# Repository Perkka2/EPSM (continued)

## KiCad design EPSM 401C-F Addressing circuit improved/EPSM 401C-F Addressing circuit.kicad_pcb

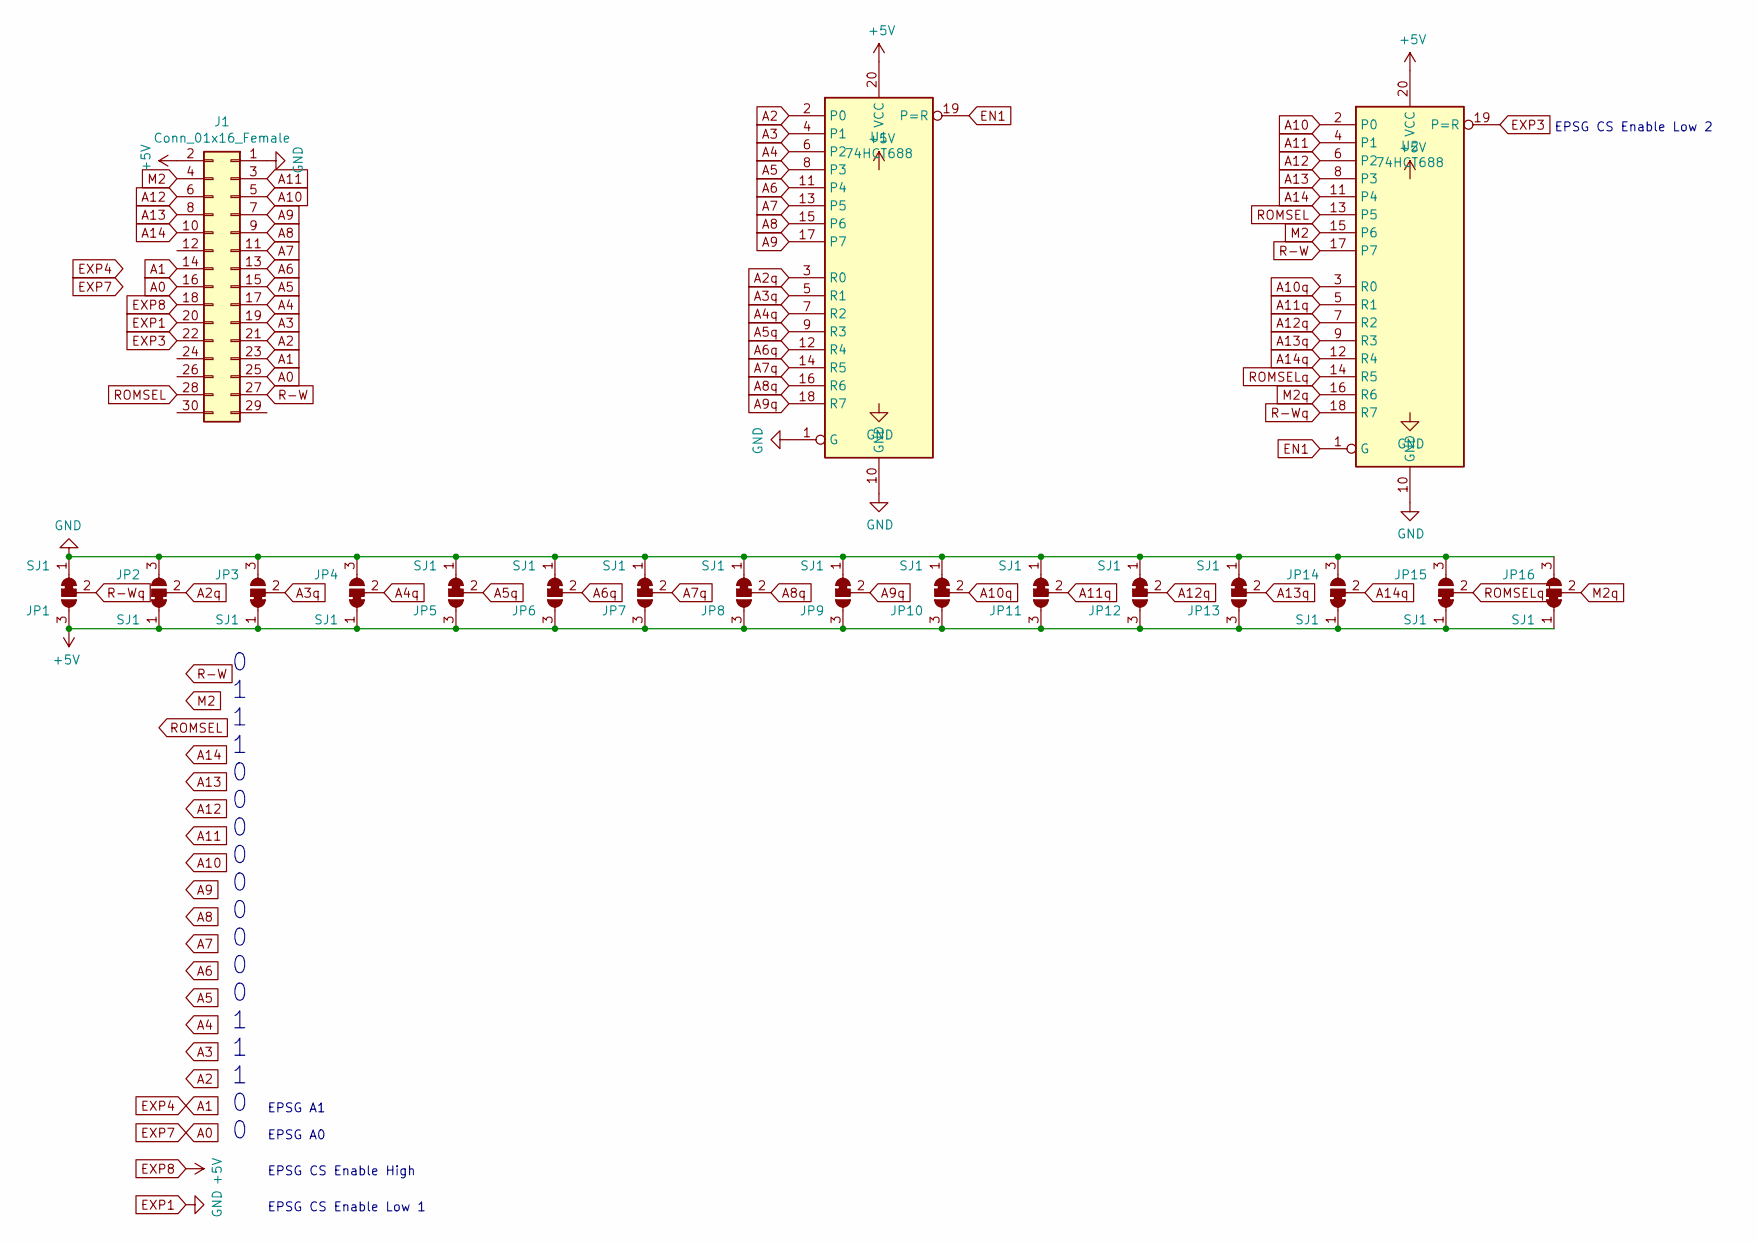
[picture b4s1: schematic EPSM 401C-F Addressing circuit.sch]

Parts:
J1: Conn_01x16_Female; PinSocket_2x15_P2.54mm_Vertical_SMD
JP1, JP2, JP3, JP4, JP5, JP6, JP7, JP8, JP9, JP10, JP11, JP12, JP13, JP14, JP15, JP16: SJ1; SolderJumper-3_P1.3mm_Bridged12_RoundedPad1.0x1.5mm
U1, U2: 74HCT688; SMDIP-20_W9.53mm_Clearance8mm

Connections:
A0: J1.16, J1.25
A1: J1.14, J1.23
A2: J1.21, U1.2 (P0)
A2q: JP2.2 (C), U1.3 (R0)
A3: J1.19, U1.4 (P1)
A3q: JP3.2 (C), U1.5 (R1)
A4: J1.17, U1.6 (P2)
A4q: JP4.2 (C), U1.7 (R2)
A5: J1.15, U1.8 (P3)
A5q: JP5.2 (C), U1.9 (R3)
A6: J1.13, U1.11 (P4)
A6q: JP6.2 (C), U1.12 (R4)
A7: J1.11, U1.13 (P5)
A7q: JP7.2 (C), U1.14 (R5)
A8: J1.9, U1.15 (P6)
A8q: JP8.2 (C), U1.16 (R6)
A9: J1.7, U1.17 (P7)
A9q: JP9.2 (C), U1.18 (R7)
A10: J1.5, U2.2 (P0)
A10q: JP10.2 (C), U2.3 (R0)
A11: J1.3, U2.4 (P1)
A11q: JP11.2 (C), U2.5 (R1)
A12: J1.6, U2.6 (P2)
A12q: JP12.2 (C), U2.7 (R2)
A13: J1.8, U2.8 (P3)
A13q: JP13.2 (C), U2.9 (R3)
A14: J1.10, U2.11 (P4)
A14q: JP14.2 (C), U2.12 (R4)
EN1: U1.19 (P=R), U2.1 (G)
EXP1: J1.1, J1.20, JP1.1 (A), JP2.3 (B), JP3.3 (B), JP4.3 (B), JP5.1 (A), JP6.1 (A), JP7.1 (A), JP8.1 (A), JP9.1 (A), JP10.1 (A), JP11.1 (A), JP12.1 (A), JP13.1 (A), JP14.3 (B), JP15.3 (B), JP16.3 (B), U1.1 (G), U1.10 (GND), U2.10 (GND)
EXP3: J1.22, U2.19 (P=R)
EXP8: J1.2, J1.18, JP1.3 (B), JP2.1 (A), JP3.1 (A), JP4.1 (A), JP5.3 (B), JP6.3 (B), JP7.3 (B), JP8.3 (B), JP9.3 (B), JP10.3 (B), JP11.3 (B), JP12.3 (B), JP13.3 (B), JP14.1 (A), JP15.1 (A), JP16.1 (A), U1.20 (VCC), U2.20 (VCC)
M2: J1.4, U2.15 (P6)
M2q: JP16.2 (C), U2.16 (R6)
R-W: J1.27, U2.17 (P7)
R-Wq: JP1.2 (C), U2.18 (R7)
ROMSEL: J1.28, U2.13 (P5)
ROMSELq: JP15.2 (C), U2.14 (R5)

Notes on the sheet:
0 1 1 1 0 0 0 0 0 0 0 0 0 1 1 1 0 0
EPSG A1
EPSG A0
EPSG CS Enable High
EPSG CS Enable Low 1
EPSG CS Enable Low 2

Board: 2 copper layers, 19 parts (0 on the bottom side), 38 nets, no tracks yet.

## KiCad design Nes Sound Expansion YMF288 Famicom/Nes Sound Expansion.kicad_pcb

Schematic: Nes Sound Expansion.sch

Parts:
BU9480F1: BU9480F; SOIC-8_5.275x5.275mm_P1.27mm
C1, C6, C8, C9: 10uF; C_0504_1310Metric_Pad0.83x1.28mm_HandSolder
C2: 10u; CP_Elec_4x5.3
C3, C4, C5, C7: 68pF; C_0504_1310Metric_Pad0.83x1.28mm_HandSolder
J1: OUT; PinHeader_1x02_P2.54mm_Vertical
J2: EXP 1-30; PinSocket_2x15_P2.54mm_Vertical_SMD
J3: EXP 1-30; Famicon CardEdge
J4: 31-60; Famicon CardEdge
J8: EXP 25-48; Famicon CardEdge
J9: EXP 1-24; Famicon CardEdge
R1, R2, R7: 47k; R_0805_2012Metric_Pad1.20x1.40mm_HandSolder
R3: 4.7k; R_0805_2012Metric_Pad1.20x1.40mm_HandSolder
R4, R5, R8, R9, R12, R13, R14: 1k; R_0805_2012Metric_Pad1.20x1.40mm_HandSolder
R6: 3k; R_0805_2012Metric_Pad1.20x1.40mm_HandSolder
U1: 74LS139; SOIC-16_3.9x9.9mm_P1.27mm
U2: 74LS132; SOIC-14_3.9x8.7mm_P1.27mm
U3: LM321; SOT-23-5
U6, U7: 74LS174; SOIC-16_3.9x9.9mm_P1.27mm
U8, U9, U10: 74LS257; SOIC-16_3.9x9.9mm_P1.27mm
X1: CXO_DIP8; Oscillator_SMD_SeikoEpson_SG8002CA-4Pin_7.0x5.0mm_HandSolde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
YMF288: YMF288

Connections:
4016_EN: R12.2, R13.2, U7.15 (Q5), U8.1 (S), U9.1 (S), U10.1 (S)
+5V: BU9480F1.8, J2.2, J4.1, J8.1, R1.1, R4.1, U1.16 (VCC), U2.14 (VCC), U3.5 (V+), U6.16 (VCC), U7.14 (D5), U7.16 (VCC), U8.16 (VCC), U9.16 (VCC), U10.16 (VCC), X1.4 (VCC), YMF288.12, YMF288.19, YMF288.22, YMF288.27
+5VA: J3.30, J9.30
A0: J2.25, J3.13, J9.13
A0_Chip: U10.7 (Zb), YMF288.20
A0_buf: U6.12 (Q4), U10.6 (I1b)
A1: J2.23, J3.12, J9.12
A1_Chip: U10.4 (Za), YMF288.21
A1_buf: U6.15 (Q5), U10.3 (I1a)
A2: J2.21, J3.11, J9.11
A3: J2.19, J3.10, J9.10
A4: J2.17, J3.9, J9.9
A5: J2.15, J3.8, J9.8
A6: J2.13, J3.7, J9.7
A7: J2.11, J3.6, J9.6
A8: J2.9, J3.5, J9.5
A9: J2.7, J3.4, J9.4
A10: J2.5, J3.3, J9.3
A11: J2.3, J3.2, J9.2
A12: J2.6, J4.3, J8.3
A13: J2.8, J4.4, J8.4
A14: J2.10, J4.5, J8.5
Addr_A1: J2.14, U10.2 (I0a)
Addr_A13: J2.16, U10.5 (I0b)
Addr_A14: J2.18, U1.14 (A0)
Addr_R-W: J2.22, U1.13 (A1)
Addr_ROMSEL: J2.20, U1.15 (E)
Aud: J4.15, J8.15
AudIn: J8.16, R6.1, R9.1
CIRAM_A10: J3.18, J9.18
CIRAM_CE: J4.18, J8.18
CS_: U1.11 (O1), U10.14 (I0c)
CS_Chip: U10.12 (Zc), YMF288.17
CS_buf: U2.6, U10.13 (I1c)
D0: J4.13, J8.13, U9.2 (I0a)
D0_Chip: U9.4 (Za), YMF288.2
D0_buf: U7.2 (Q0), U9.3 (I1a)
D1: J4.12, J8.12, U9.5 (I0b)
D1_Chip: U9.7 (Zb), YMF288.3
D1_buf: U7.5 (Q1), U9.6 (I1b)
D2: J4.11, J8.11, U6.14 (D5), U9.14 (I0c)
D2_Chip: U9.12 (Zc), YMF288.4
D2_buf: U7.7 (Q2), U9.13 (I1c)
D3: J4.10, J8.10, U6.13 (D4), U9.11 (I0d)
D3_Chip: U9.9 (Zd), YMF288.5
D3_buf: U7.10 (Q3), U9.10 (I1d)
D4: J4.9, J8.9, U6.3 (D0), U7.3 (D0), U8.2 (I0a)
D4_Chip: U8.4 (Za), YMF288.6
D4_buf: U6.2 (Q0), U8.3 (I1a)
D5: J4.8, J8.8, U6.4 (D1), U7.4 (D1), U8.5 (I0b)
D5_Chip: U8.7 (Zb), YMF288.7
D5_buf: U6.5 (Q1), U8.6 (I1b)
D6: J4.7, J8.7, U6.6 (D2), U7.6 (D2), U8.14 (I0c)
D6_Chip: U8.12 (Zc), YMF288.8
D6_buf: U6.7 (Q2), U8.13 (I1c)
D7: J4.6, J8.6, U6.11 (D3), U7.11 (D3), U8.11 (I0d)
D7_Chip: U8.9 (Zd), YMF288.9
D7_buf: U6.10 (Q3), U8.10 (I1d)
FF_Reset: U2.8, U6.1 (~Mr), U7.1 (~Mr)
GND: BU9480F1.3, C1.1, C2.2, C3.1, C4.1, C5.1, C7.1, C8.2, J1.1, J2.1, J3.1, J9.1, R2.2, U1.1 (E), U1.8 (GND), U2.7 (GND), U3.2 (V-), U6.8 (GND), U7.8 (GND), U8.8 (GND), U8.15 (OE), U9.8 (GND), U9.15 (OE), U10.8 (GND), U10.15 (OE), X1.2 (GND), YMF288.1, YMF288.14, YMF288.16, YMF288.18
GND1: J3.16, J9.16
IRQ: J3.15, J9.15, YMF288.15
M2: J2.4, J4.2, J8.2
unnamed: BU9480F1.1, R8.2
unnamed: BU9480F1.2, C2.1
unnamed: BU9480F1.4, R5.1
unnamed: BU9480F1.5, YMF288.26
unnamed: BU9480F1.6, YMF288.24
unnamed: BU9480F1.7, YMF288.23
unnamed: C1.2, R4.2, YMF288.11
unnamed: C3.2, R12.1, U2.4
unnamed: C4.2, R13.1, U2.1, U2.2
unnamed: C5.2, R14.1, U2.12, U2.13
unnamed: C6.1, R5.2, R8.1
unnamed: C6.2, C7.2, R1.2, R2.1, U3.1 (+)
unnamed: C8.1, R3.2
unnamed: C9.1, R9.2
unnamed: C9.2, R7.2, U3.4
unnamed: J4.16, R6.2
unnamed: R3.1, R7.1, U3.3 (-)
unnamed: R14.2, U2.3, U2.5
unnamed: U2.9, U2.10, U2.11
unnamed: X1.3 (OUT), YMF288.28
OUT1: J1.2, U1.2 (A0), U1.3 (A1), U6.9 (Cp)
OUT1_: U1.7 (O3), U7.9 (Cp)
PPU_A0: J3.25, J9.25
PPU_A1: J3.24, J9.24
PPU_A2: J3.23, J9.23
PPU_A3: J3.22, J9.22
PPU_A4: J3.21, J9.21
PPU_A5: J3.20, J9.20
PPU_A6: J3.19, J9.19
PPU_A7: J4.20, J8.20
PPU_A8: J4.21, J8.21
PPU_A9: J4.22, J8.22
PPU_A10: J4.23, J8.23
PPU_A11: J4.24, J8.24
PPU_A12: J4.25, J8.25
PPU_A13: J4.26, J8.26
PPU_A13_: J4.19, J8.19
PPU_D0: J3.26, J9.26
PPU_D1: J3.27, J9.27
PPU_D2: J3.28, J9.28
PPU_D3: J3.29, J9.29
PPU_D4: J4.30, J8.30
PPU_D5: J4.29, J8.29
PPU_D6: J4.28, J8.28
PPU_D7: J4.27, J8.27
PPU_RD: J3.17, J9.17
PPU_WR: J4.17, J8.17
R-W: J2.27, J3.14, J9.14
ROMSEL: J2.28, J4.14, J8.14

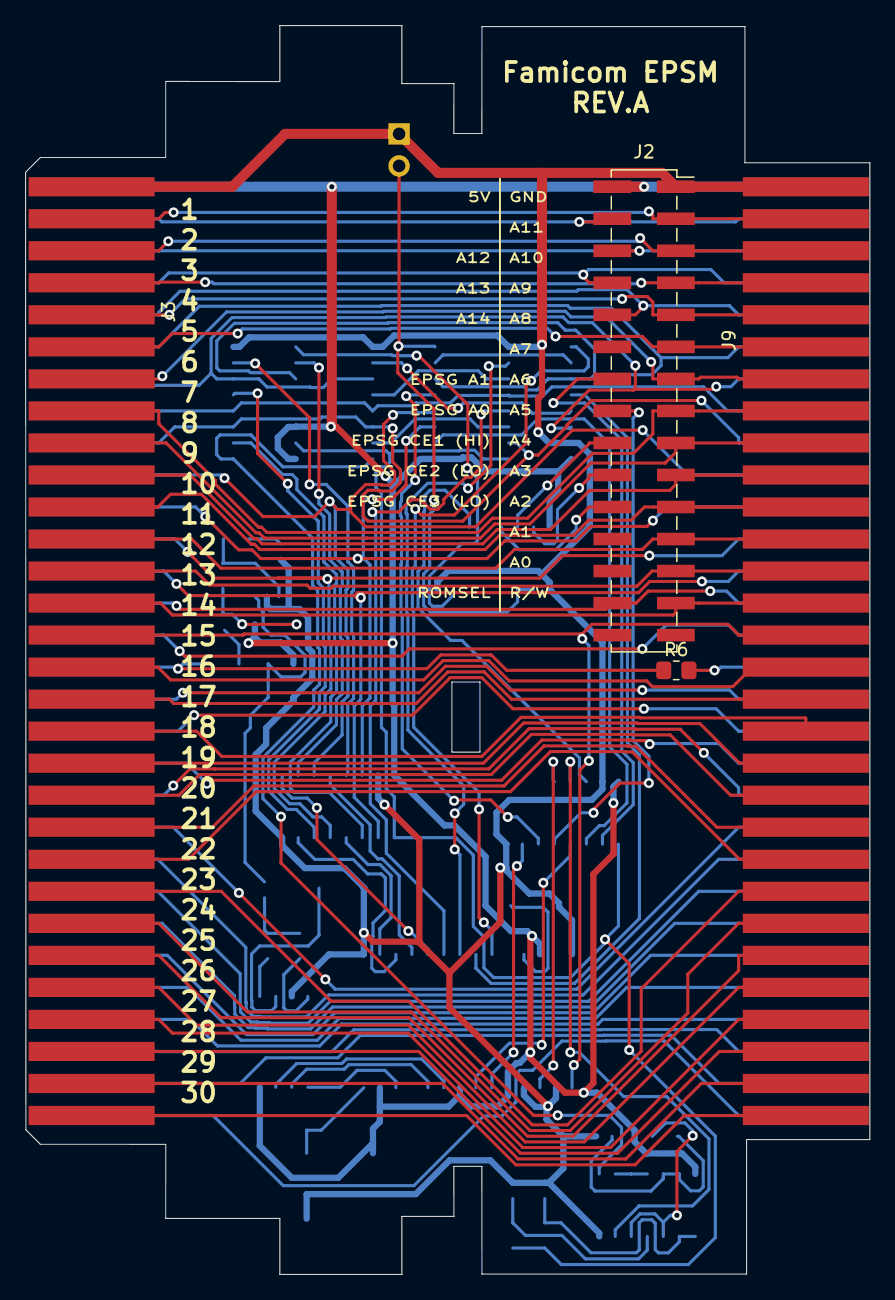
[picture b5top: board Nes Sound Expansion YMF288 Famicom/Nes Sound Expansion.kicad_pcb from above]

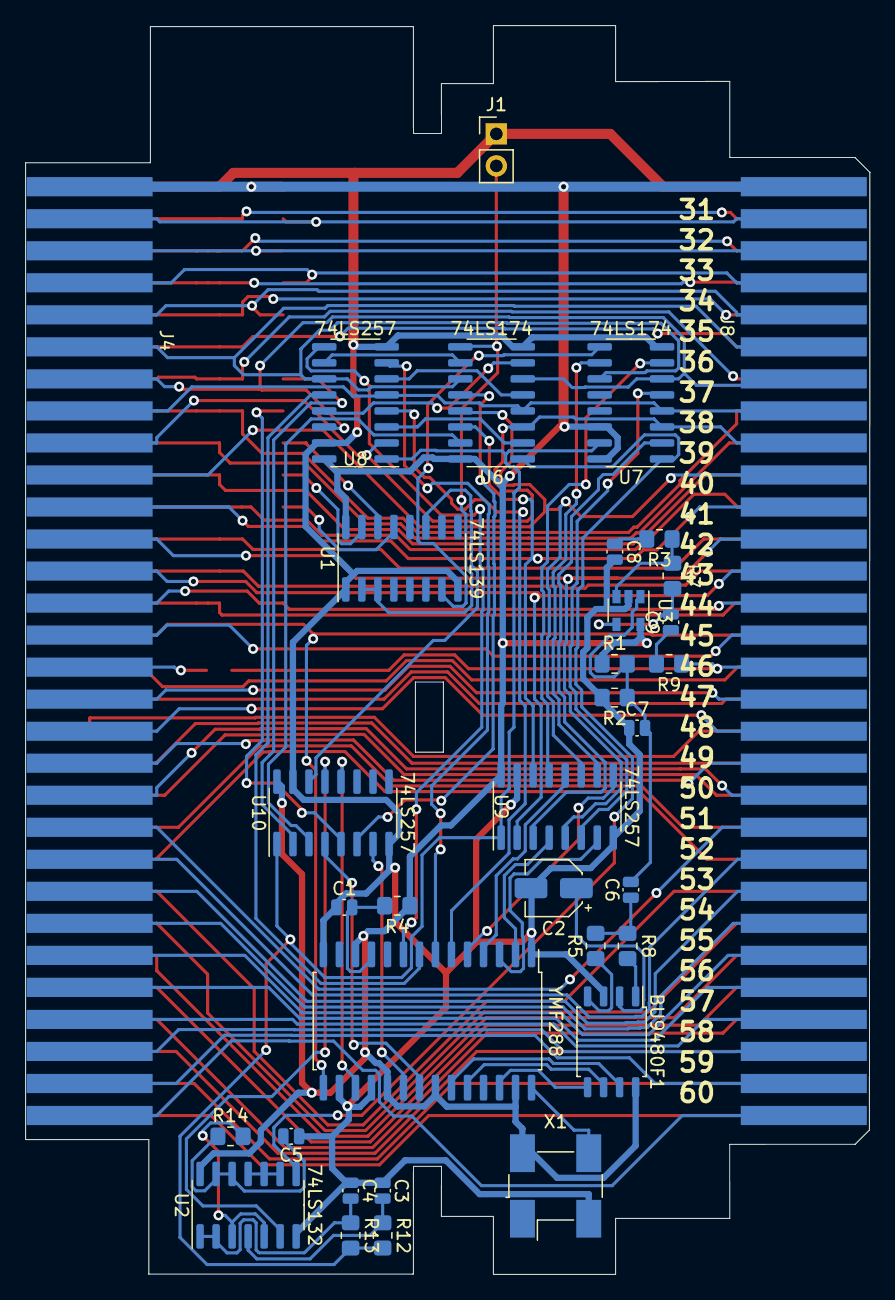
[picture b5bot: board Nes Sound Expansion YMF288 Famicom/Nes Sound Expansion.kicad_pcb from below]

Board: 2 copper layers, 67.0 x 99.0 mm, 38 parts (34 on the bottom side), 112 nets.

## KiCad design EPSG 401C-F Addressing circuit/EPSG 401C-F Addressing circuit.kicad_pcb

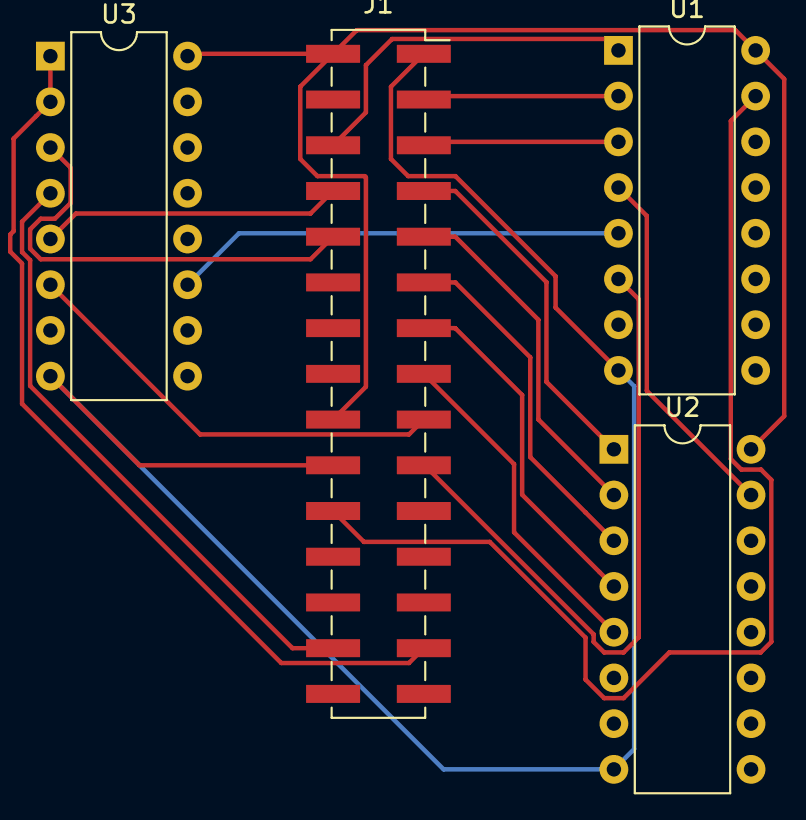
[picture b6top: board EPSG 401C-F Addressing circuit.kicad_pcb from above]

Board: 2 copper layers, 4 parts (0 on the bottom side), 22 nets.

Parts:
J1: Conn_01x16_Female; PinSocket_2x15_P2.54mm_Vertical_SMD
U1, U2, U3: 74LS138; DIP-16_W7.62mm

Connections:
A0: J1.16, J1.25
A1: J1.14, J1.23
A2: J1.21, U2.6
A3: J1.19, U1.6
A4: J1.17, U3.6
A5: J1.15, U2.5
A6: J1.13, U2.4
A7: J1.11, U2.3
A8: J1.9, U2.2
A9: J1.7, U2.1
A10: J1.5, U1.3
A11: J1.3, U1.2
A12: J1.6, U1.1
A13: J1.8, U3.5
A14: J1.10, U3.3
EN1: U1.4, U2.15
EN2: U1.5, U3.11
EXP1: J1.1, J1.20, U1.8, U2.8, U3.8
EXP3: J1.22, U1.15
EXP8: J1.2, J1.18, U1.16, U2.16, U3.16
R-W: J1.27, U3.1, U3.2
ROMSEL: J1.28, U3.4

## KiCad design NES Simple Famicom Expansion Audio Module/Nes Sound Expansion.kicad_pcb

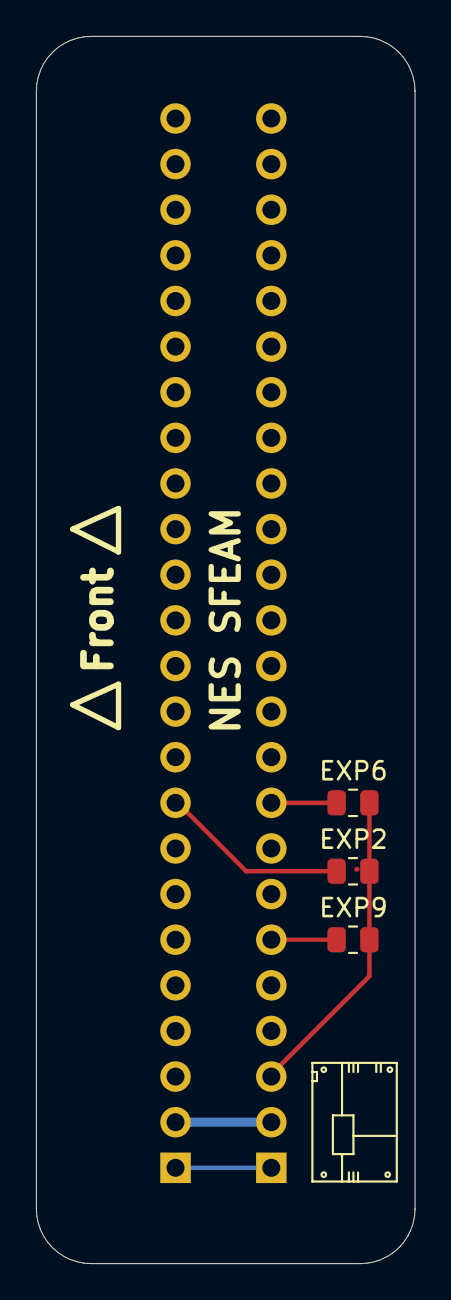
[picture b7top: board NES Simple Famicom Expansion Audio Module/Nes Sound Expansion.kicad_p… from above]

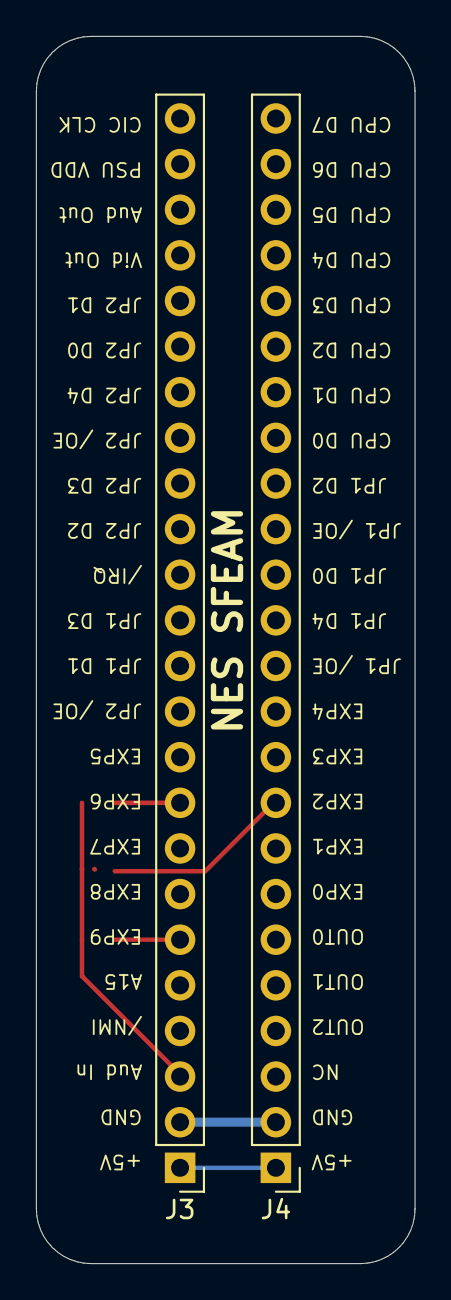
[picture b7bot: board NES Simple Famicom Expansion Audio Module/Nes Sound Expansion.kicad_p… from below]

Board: 2 copper layers, 21.1 x 68.3 mm, 5 parts (2 on the bottom side), 6 nets.

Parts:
J3: EXP 1-24; PinHeader_1x24_P2.54mm_Vertical
J4: EXP 25-48; PinHeader_1x24_P2.54mm_Vertical
R1, R2, R3: 47k; R_0805_2012Metric

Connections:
AudIn: J3.3, R1.2, R2.2, R3.2
GND: J3.2, J4.2
unnamed: J3.1, J4.1
unnamed: J3.6, R3.1
unnamed: J3.9, R1.1
unnamed: J4.9, R2.1

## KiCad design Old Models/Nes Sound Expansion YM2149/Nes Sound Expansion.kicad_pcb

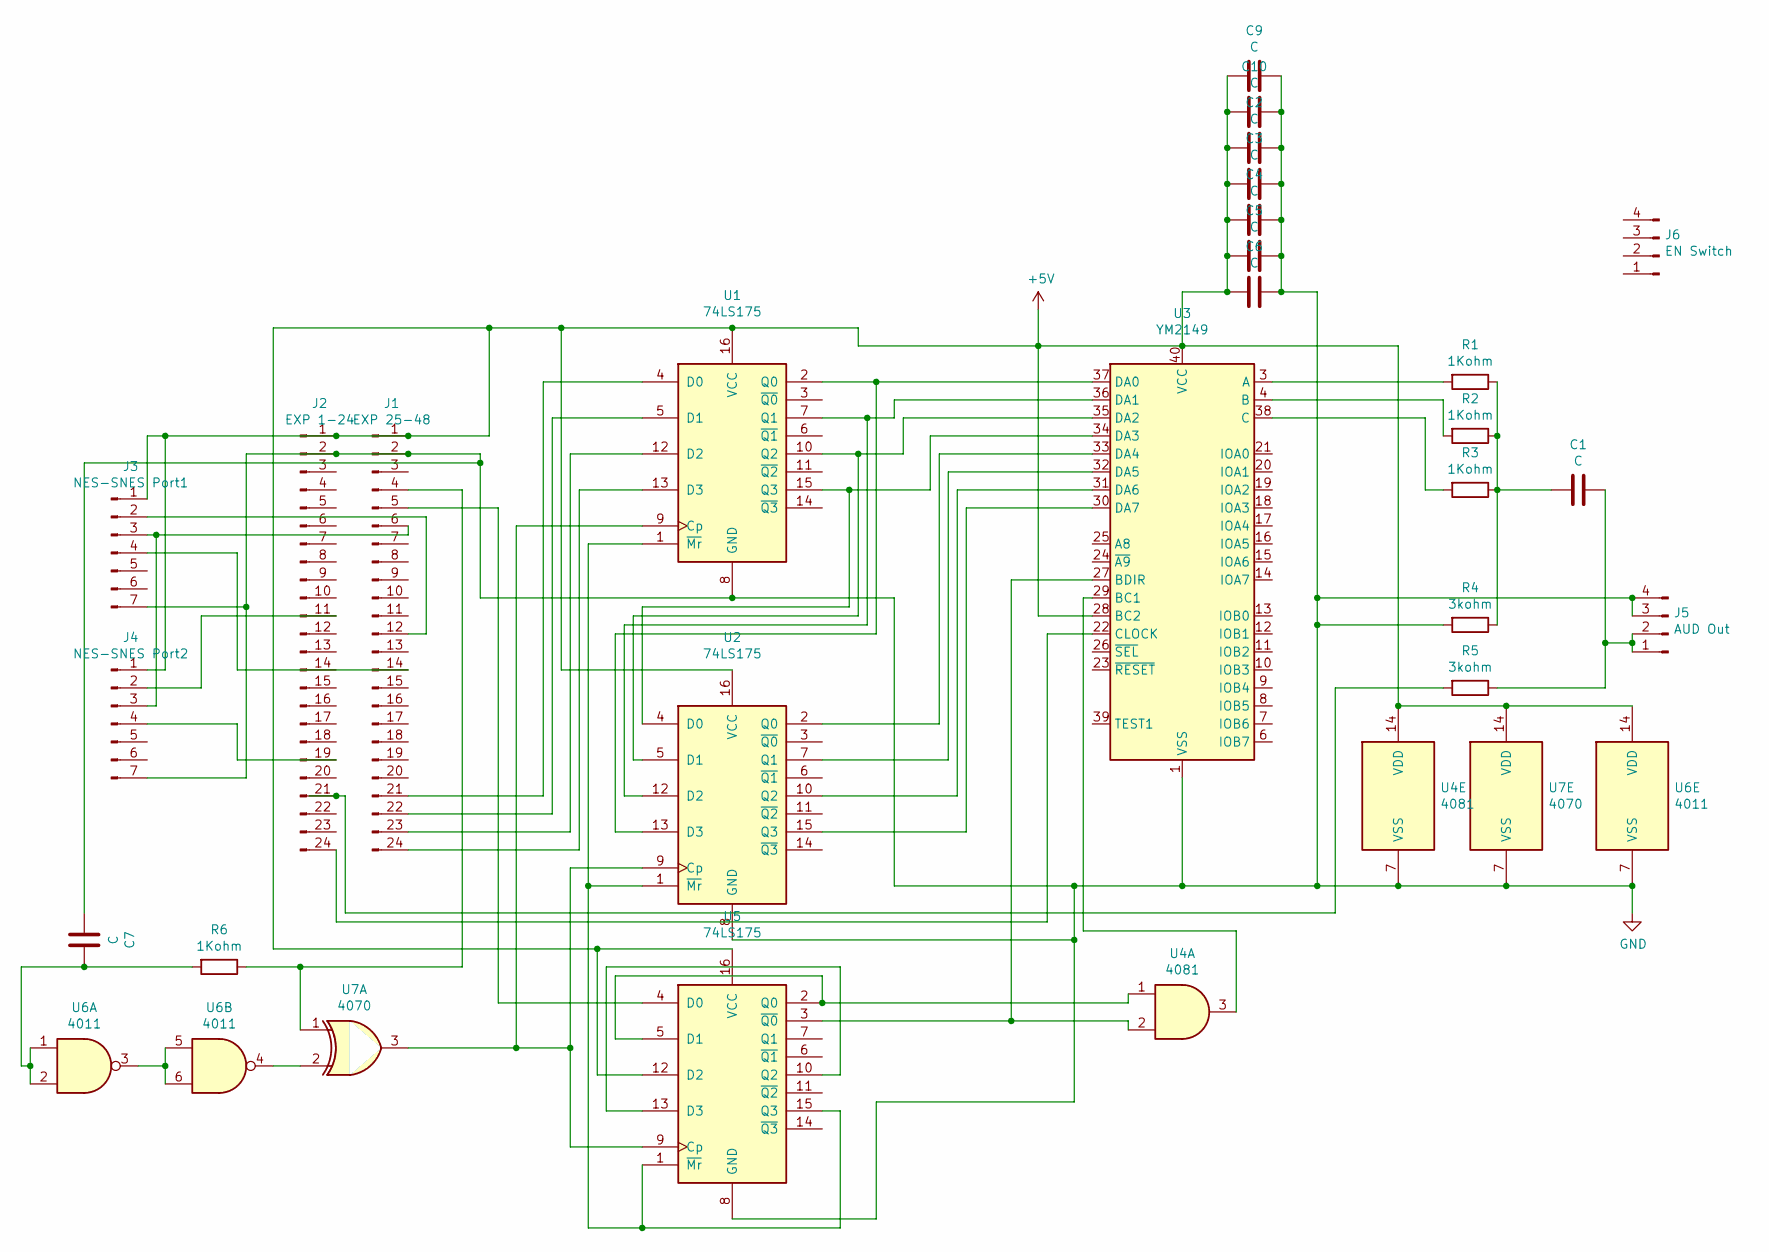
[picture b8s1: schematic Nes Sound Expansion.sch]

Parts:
C1, C2, C3, C4, C5, C6, C7, C9, C10: C; C_Disc_D5.1mm_W3.2mm_P5.00mm
J1: EXP 25-48; PinHeader_1x24_P2.54mm_Vertical
J2: EXP 1-24; PinHeader_1x24_P2.54mm_Vertical
J3: NES-SNES Port1; PinHeader_1x07_P2.54mm_Vertical
J4: NES-SNES Port2; PinHeader_1x07_P2.54mm_Vertical
J5: AUD Out; PinHeader_1x04_P2.54mm_Vertical
J6: EN Switch; PinHeader_1x04_P2.54mm_Vertical
R1, R2, R3, R6: 1Kohm; R_Axial_DIN0207_L6.3mm_D2.5mm_P10.16mm_Horizontal
R4, R5: 3kohm; R_Axial_DIN0207_L6.3mm_D2.5mm_P10.16mm_Horizontal
U1, U2, U5: 74LS175; DIP-16_W7.62mm
U3: YM2149; DIP-40_W15.24mm
U4: 4081; DIP-14_W7.62mm
U6: 4011; DIP-14_W7.62mm
U7: 4070; DIP-14_W7.62mm

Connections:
+5V: C2.2, C3.2, C4.2, C5.2, C6.2, C9.2, C10.2, J1.1, J2.1, J3.1, J4.1, U1.16 (VCC), U2.16 (VCC), U3.28 (BC2), U3.40 (VCC), U4.14 (VDD), U5.12 (D2), U5.16 (VCC), U6.14 (VDD), U7.14 (VDD)
GND: C2.1, C3.1, C4.1, C5.1, C6.1, C7.2, C9.1, C10.1, J1.2, J2.2, J3.7, J4.7, J5.3, J5.4, R4.2, U1.8 (GND), U2.8 (GND), U3.1 (VSS), U4.7 (VSS), U5.8 (GND), U6.7 (VSS), U7.7 (VSS)
unnamed: C1.1, J5.1, J5.2, R5.1
unnamed: C1.2, R1.1, R2.1, R3.1, R4.1
unnamed: C7.1, R6.2, U6.1, U6.2
unnamed: J1.4, R6.1, U7.1
unnamed: J1.5, U5.4 (D0)
unnamed: J1.6, J3.3, J4.3
unnamed: J1.12, J3.2
unnamed: J1.14, J3.4
unnamed: J1.21, U1.4 (D0)
unnamed: J1.22, U1.5 (D1)
unnamed: J1.23, U1.12 (D2)
unnamed: J1.24, U1.13 (D3)
unnamed: J2.11, J4.2
unnamed: J2.19, J4.4
unnamed: J2.21, R5.2
unnamed: J2.24, U3.22 (CLOCK)
unnamed: R1.2, U3.3 (A)
unnamed: R2.2, U3.4 (B)
unnamed: R3.2, U3.38 (C)
unnamed: U1.1 (~Mr), U2.1 (~Mr), U5.1 (~Mr), U5.15 (Q3)
unnamed: U1.2 (Q0), U2.13 (D3), U3.37 (DA0)
unnamed: U1.7 (Q1), U2.12 (D2), U3.36 (DA1)
unnamed: U1.9 (Cp), U2.9 (Cp), U5.9 (Cp), U7.3
unnamed: U1.10 (Q2), U2.5 (D1), U3.35 (DA2)
unnamed: U1.15 (Q3), U2.4 (D0), U3.34 (DA3)
unnamed: U2.2 (Q0), U3.33 (DA4)
unnamed: U2.7 (Q1), U3.32 (DA5)
unnamed: U2.10 (Q2), U3.31 (DA6)
unnamed: U2.15 (Q3), U3.30 (DA7)
unnamed: U3.27 (BDIR), U4.2, U5.3 (~Q0)
unnamed: U3.29 (BC1), U4.3
unnamed: U4.1, U5.2 (Q0), U5.5 (D1)
unnamed: U5.10 (Q2), U5.13 (D3)
unnamed: U6.3, U6.5, U6.6
unnamed: U6.4, U7.2

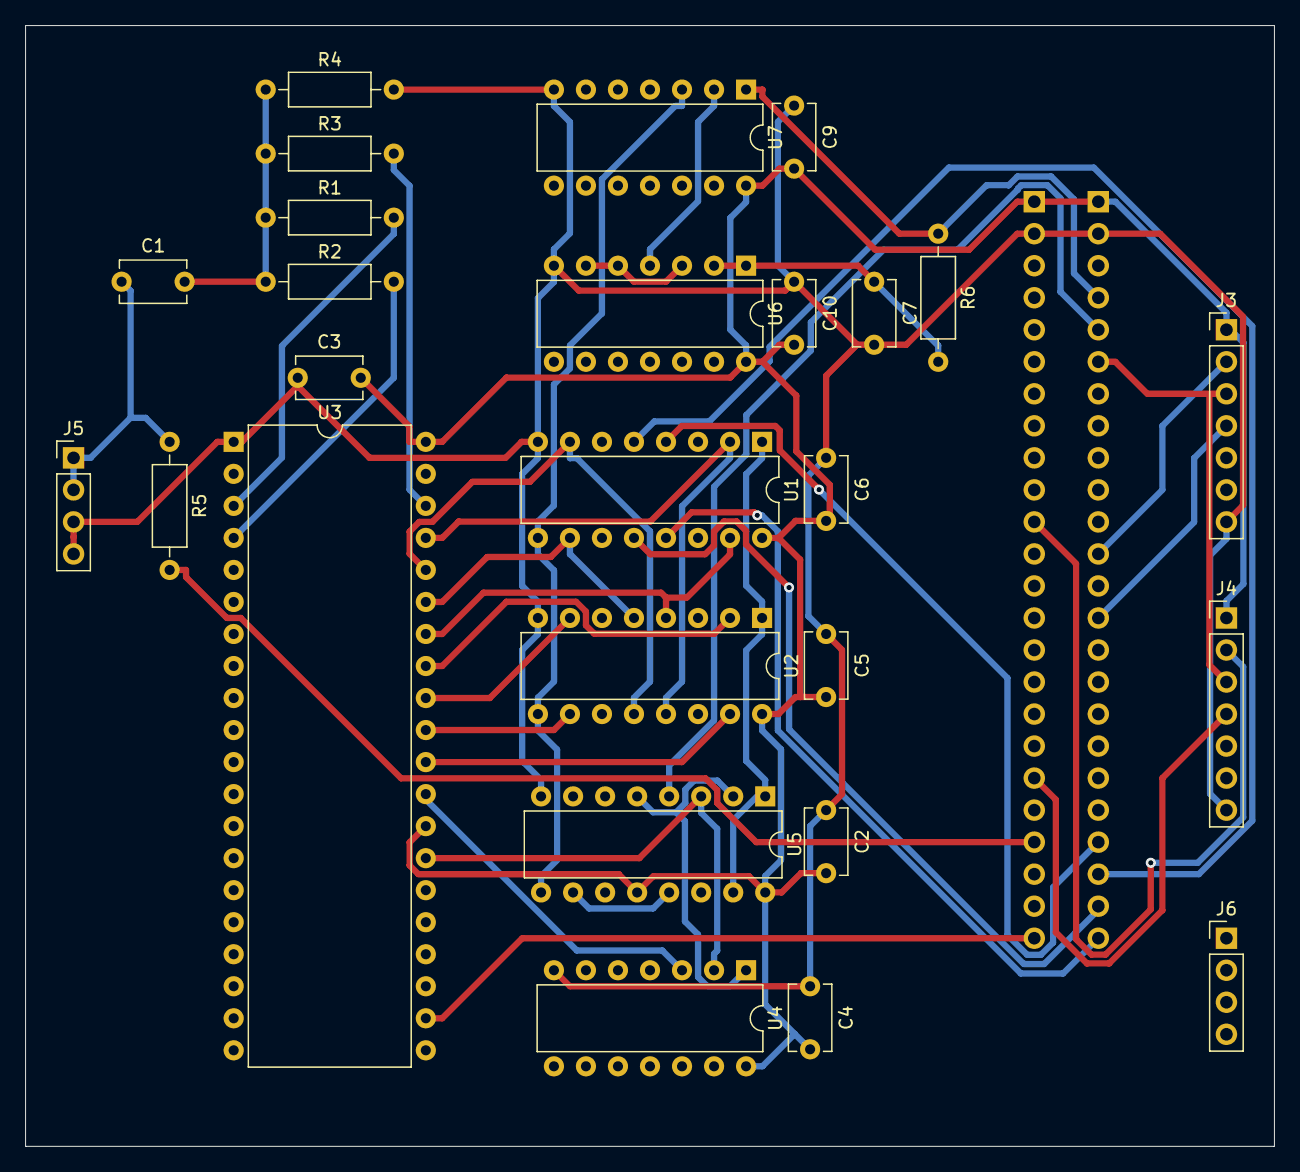
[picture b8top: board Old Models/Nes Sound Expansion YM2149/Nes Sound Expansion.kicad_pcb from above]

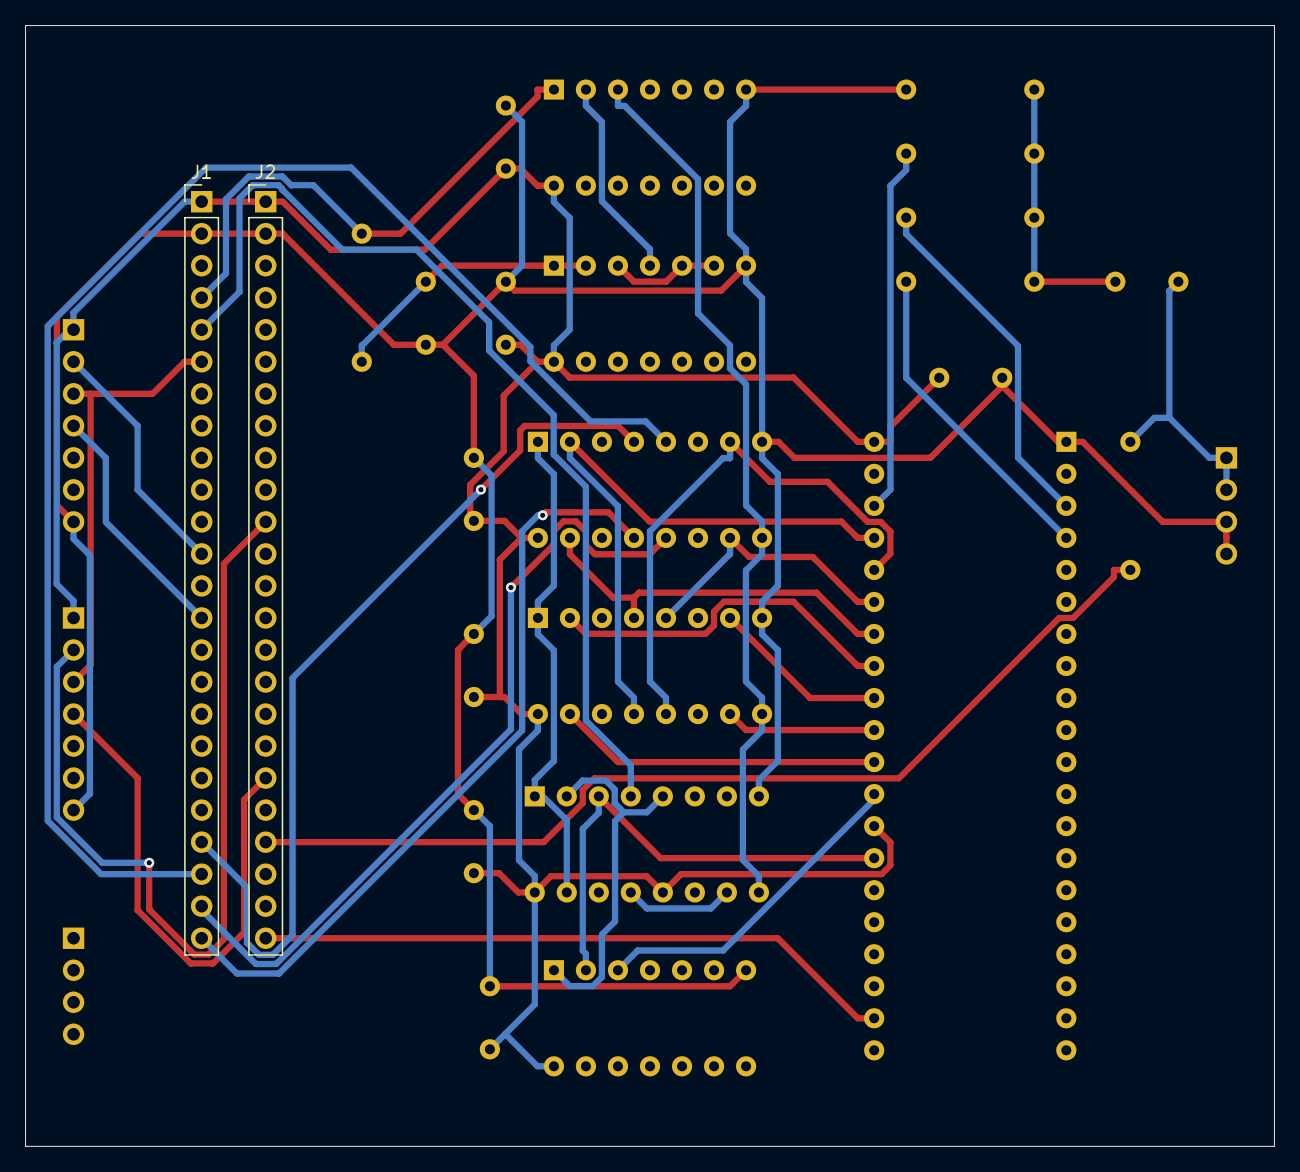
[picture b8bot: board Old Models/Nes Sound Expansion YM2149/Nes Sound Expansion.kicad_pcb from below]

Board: 2 copper layers, 99.1 x 88.9 mm, 28 parts (2 on the bottom side), 37 nets.

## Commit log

2021-04-23 Uploaded all current files
2021-04-23 changed reset circuit
2021-05-06 Fixed floating signals and famicom exp audio
    Addressing issues caused by floating signals when a cart without hardware addressing is used
    Added famicom expansion resistors to all 3 popular EXP pins.
2021-05-06 minor update
2021-05-07 Updated mixing on the Famicom version
2021-05-15 Addressing circuit added for using 401C-401F address range
2021-05-16 Added IRQ from the YMF288
2021-05-24 Added logo, 3.5mm 3d module, removed unused stuff
2021-05-26 Redesigned to fit a Famicom MMC cart and updated readme
2021-05-26 minor updates
2021-05-26 Folder rename
2021-06-11 Added amplification for both famicom and nes model
2021-09-01 Updated 401C-F addressing circuit
2021-09-01 Added M2 to the addressing circuit and famicom daughterboard connector
2022-03-10 Some example images
2022-05-11 Removed power switch and updated resistor values
2022-05-11 Forgot to press save after editing resistor values
2022-05-15 Add perpendicular Famicom PCB design
2022-05-22 Flip cartridge connection to back instead of front
2022-06-15 Updated Rev.A to Rev.A1
2022-11-19 Added improved addressing circuit
2022-12-09 Updates to the GitHub page
2022-12-09 Updates to doc
2022-12-12 doc update
2023-01-01 Update FC-H EPSM
    - Upgrade to 4 layers
    - Use same amplifier circuit as NES EPSM
    - Optimize logic chip pin assignment
2023-01-03 Reposition all SMD components to be on top
2023-01-22 Incremental improvements
    - Add ground plane around audio traces
    - Nudge audio jack for better allowance
    - Add stitching vias in audio amplifier zone
2023-01-22 Clarify EPSM chip enable and address net names
2023-01-22 Add 401C-F decoding daughterboard PCB for EPSM FC
